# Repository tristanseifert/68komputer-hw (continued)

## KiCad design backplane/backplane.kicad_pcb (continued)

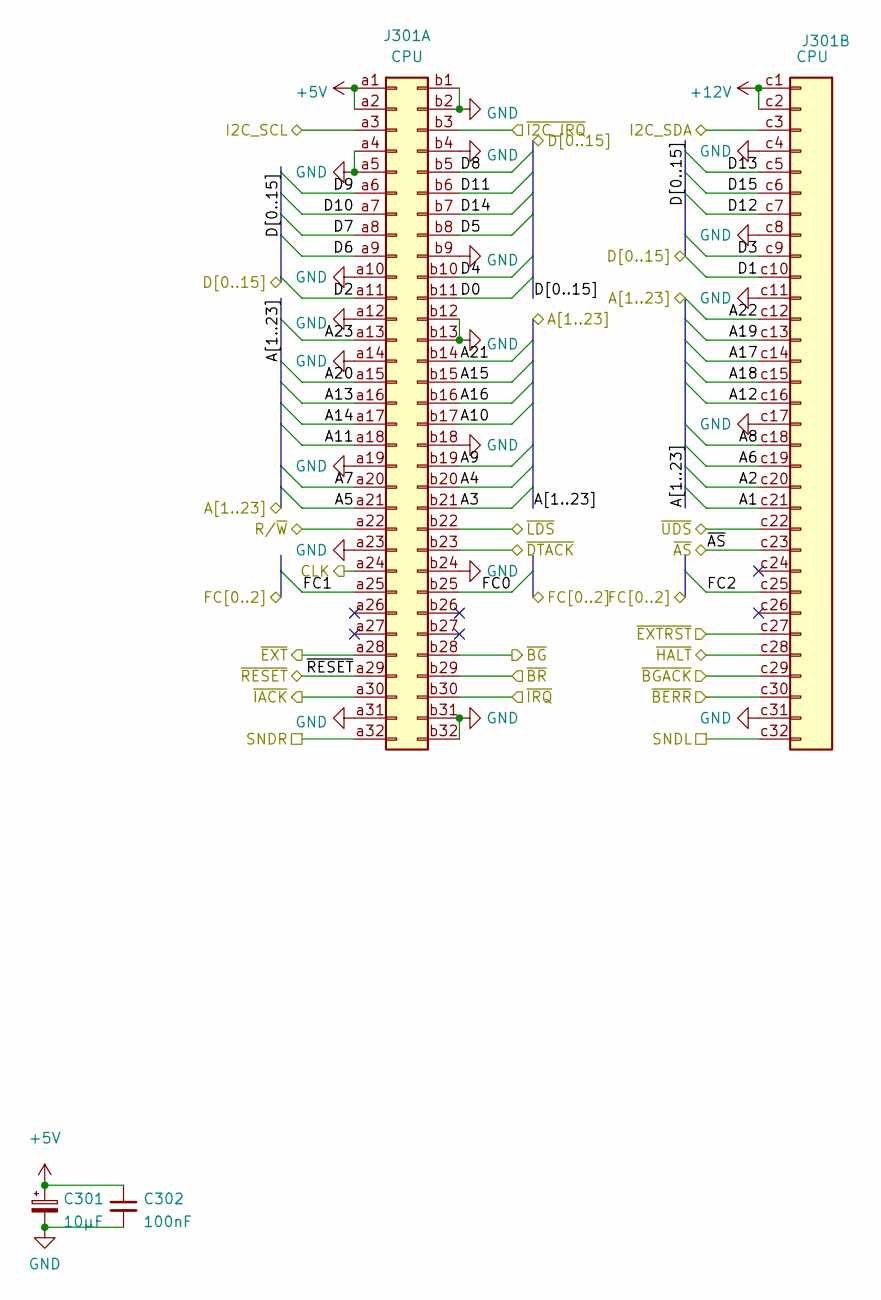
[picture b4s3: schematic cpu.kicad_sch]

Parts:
C301: 10µF; CP_EIA-3216-18_Kemet-A
C302: 100nF; C_0805_2012Metric
J301: CPU; DIN41612_C_3x32_Female_Vertical_THT

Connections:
+5V: C301.1, C302.1, J301.a1, J301.a2; also elsewhere on the board
+12V: J301.c1, J301.c2; also elsewhere on the board
/A1: J301.c21; also elsewhere on the board
/A2: J301.c20; also elsewhere on the board
/A3: J301.b21; also elsewhere on the board
/A4: J301.b20; also elsewhere on the board
/A5: J301.a21; also elsewhere on the board
/A6: J301.c19; also elsewhere on the board
/A7: J301.a20; also elsewhere on the board
/A8: J301.c18; also elsewhere on the board
/A9: J301.b19; also elsewhere on the board
/A10: J301.b17; also elsewhere on the board
/A11: J301.a18; also elsewhere on the board
/A12: J301.c16; also elsewhere on the board
/A13: J301.a16; also elsewhere on the board
/A14: J301.a17; also elsewhere on the board
/A15: J301.b15; also elsewhere on the board
/A16: J301.b16; also elsewhere on the board
/A17: J301.c14; also elsewhere on the board
/A18: J301.c15; also elsewhere on the board
/A19: J301.c13; also elsewhere on the board
/A20: J301.a15; also elsewhere on the board
/A21: J301.b14; also elsewhere on the board
/A22: J301.c12; also elsewhere on the board
/A23: J301.a13; also elsewhere on the board
/CPU Board/CLK: J301.a24
/CPU Board/SNDL: J301.c32
/CPU Board/SNDR: J301.a32
/D0: J301.b11; also elsewhere on the board
/D1: J301.c10; also elsewhere on the board
/D2: J301.a11; also elsewhere on the board
/D3: J301.c9; also elsewhere on the board
/D4: J301.b10; also elsewhere on the board
/D5: J301.b8; also elsewhere on the board
/D6: J301.a9; also elsewhere on the board
/D7: J301.a8; also elsewhere on the board
/D8: J301.b5; also elsewhere on the board
/D9: J301.a6; also elsewhere on the board
/D10: J301.a7; also elsewhere on the board
/D11: J301.b6; also elsewhere on the board
/D12: J301.c7; also elsewhere on the board
/D13: J301.c5; also elsewhere on the board
/D14: J301.b7; also elsewhere on the board
/D15: J301.c6; also elsewhere on the board
/FC0: J301.b25; also elsewhere on the board
/FC1: J301.a25; also elsewhere on the board
/FC2: J301.c25; also elsewhere on the board
/I2C_SCL: J301.a3; also elsewhere on the board
/I2C_SDA: J301.c3; also elsewhere on the board
/R/~W: J301.a22; also elsewhere on the board
/~AS: J301.c23; also elsewhere on the board
/~BERR: J301.c30; also elsewhere on the board
/~BGACK: J301.c29; also elsewhere on the board
/~BG: J301.b28; also elsewhere on the board
/~BR: J301.b29; also elsewhere on the board
/~DTACK: J301.b23; also elsewhere on the board
/~EXTRST: J301.c27; also elsewhere on the board
/~EXT: J301.a28; also elsewhere on the board
/~HALT: J301.c28; also elsewhere on the board
/~I2C_IRQ: J301.b3
/~IACK: J301.a30; also elsewhere on the board
/~IRQ: J301.b30; also elsewhere on the board
/~LDS: J301.b22; also elsewhere on the board
/~RESET: J301.a29; also elsewhere on the board
/~UDS: J301.c22; also elsewhere on the board
GND: C301.2, C302.2, J301.a4, J301.a5, J301.a10, J301.a12, J301.a14, J301.a19, J301.a23, J301.a31, J301.b1, J301.b2, J301.b4, J301.b9, J301.b12, J301.b13, J301.b18, J301.b24, J301.b31, J301.b32, J301.c4, J301.c8, J301.c11, J301.c17, J301.c31; also elsewhere on the board

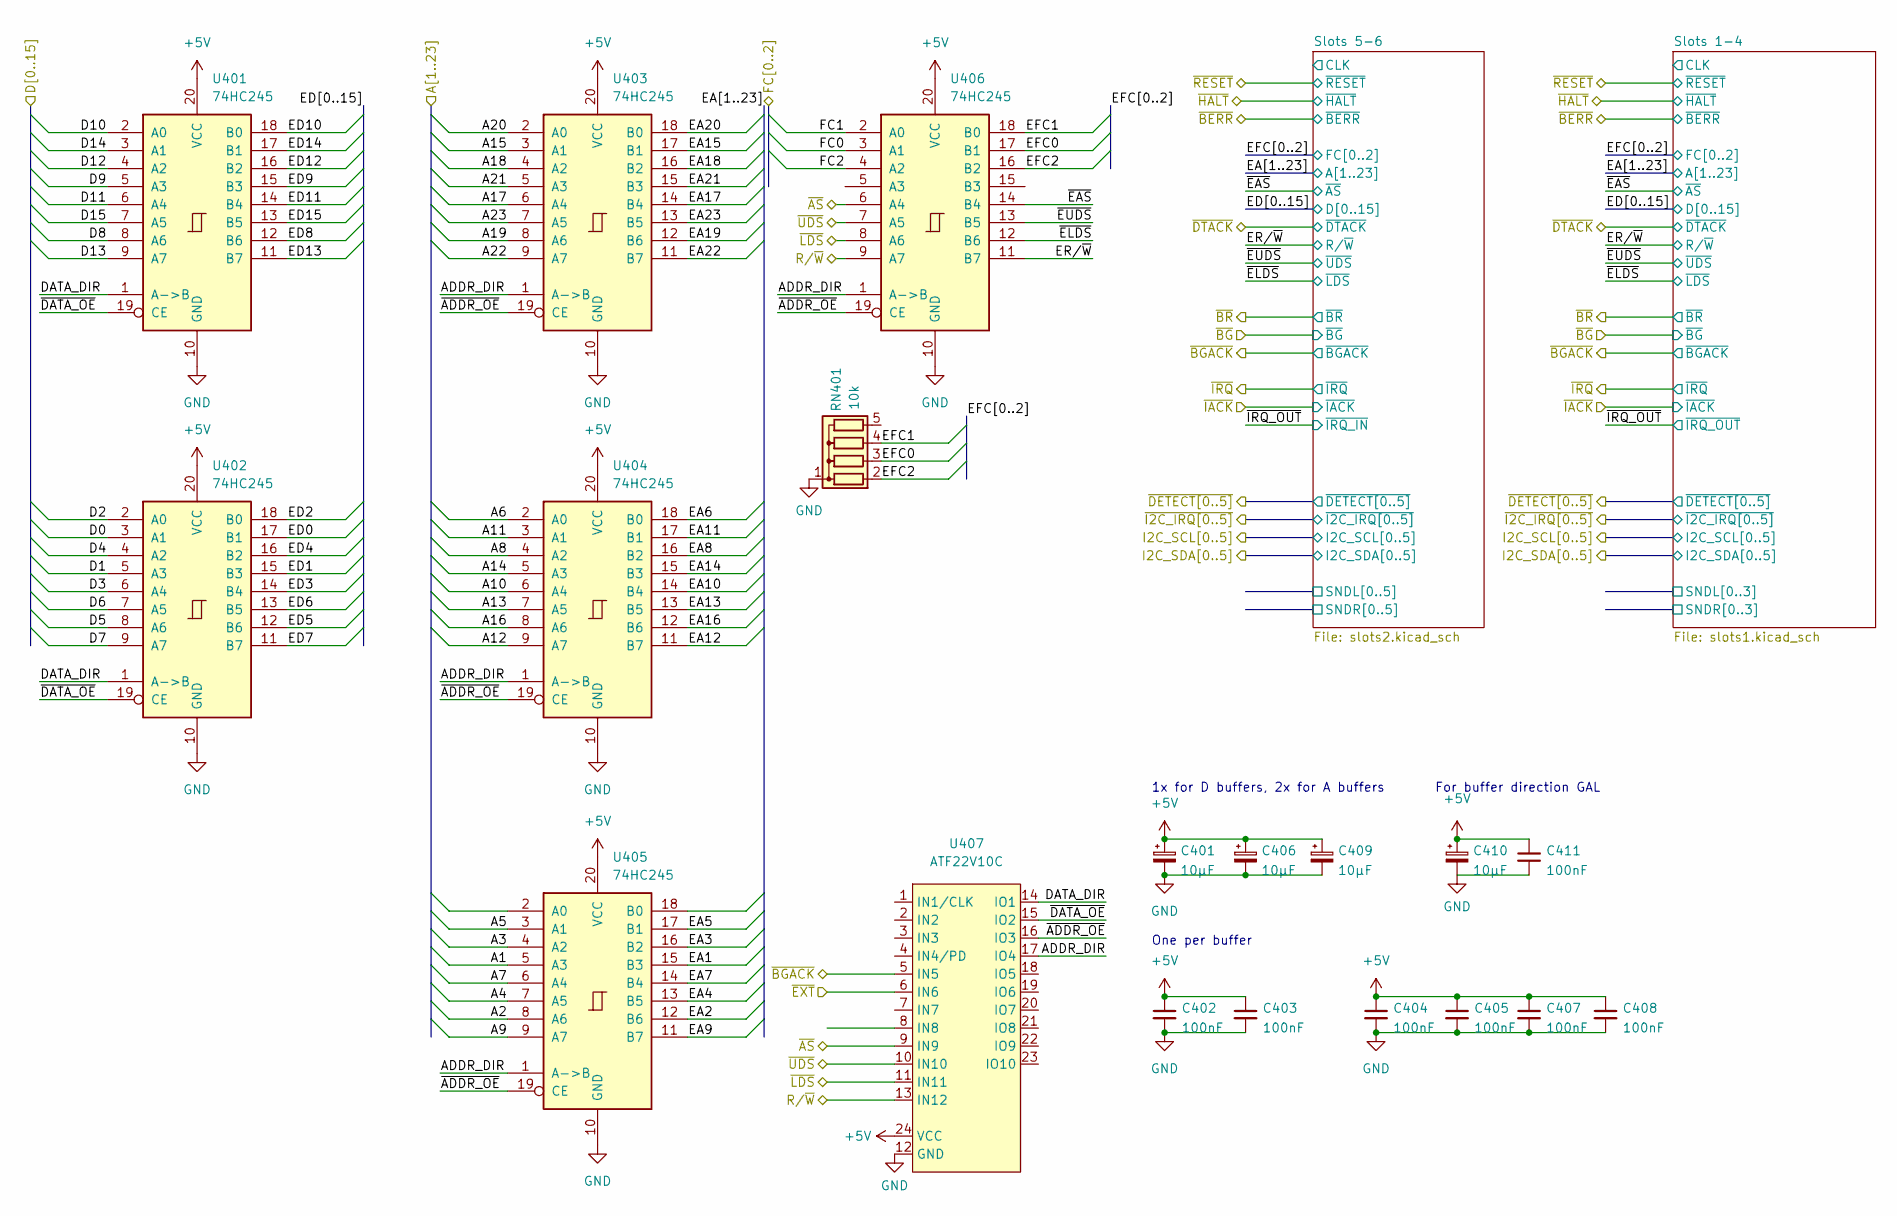
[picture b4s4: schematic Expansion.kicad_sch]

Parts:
C401, C406, C409, C410: 10µF; CP_EIA-3216-18_Kemet-A; MPN TAJA106K016RNJV
C402, C403, C404, C405, C407, C408, C411: 100nF; C_0805_2012Metric
RN401: 10k; R_Array_SIP5; MPN 4605X-101-103LF
U401, U402, U403, U404, U405, U406: 74HC245; TSSOP-20_4.4x6.5mm_P0.65mm; MPN 74HC245PW,118
U407: ATF22V10C; DIP-24_W7.62mm_Socket

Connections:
+5V: C401.1, C402.1, C403.1, C404.1, C405.1, C406.1, C407.1, C408.1, C409.1, C410.1, C411.1, U401.20 (VCC), U402.20 (VCC), U403.20 (VCC), U404.20 (VCC), U405.20 (VCC), U406.20 (VCC), U407.24 (VCC); also elsewhere on the board
/A1: U405.5 (A3); also elsewhere on the board
/A2: U405.8 (A6); also elsewhere on the board
/A3: U405.4 (A2); also elsewhere on the board
/A4: U405.7 (A5); also elsewhere on the board
/A5: U405.3 (A1); also elsewhere on the board
/A6: U404.2 (A0); also elsewhere on the board
/A7: U405.6 (A4); also elsewhere on the board
/A8: U404.4 (A2); also elsewhere on the board
/A9: U405.9 (A7); also elsewhere on the board
/A10: U404.6 (A4); also elsewhere on the board
/A11: U404.3 (A1); also elsewhere on the board
/A12: U404.9 (A7); also elsewhere on the board
/A13: U404.7 (A5); also elsewhere on the board
/A14: U404.5 (A3); also elsewhere on the board
/A15: U403.3 (A1); also elsewhere on the board
/A16: U404.8 (A6); also elsewhere on the board
/A17: U403.6 (A4); also elsewhere on the board
/A18: U403.4 (A2); also elsewhere on the board
/A19: U403.8 (A6); also elsewhere on the board
/A20: U403.2 (A0); also elsewhere on the board
/A21: U403.5 (A3); also elsewhere on the board
/A22: U403.9 (A7); also elsewhere on the board
/A23: U403.7 (A5); also elsewhere on the board
/D0: U402.3 (A1); also elsewhere on the board
/D1: U402.5 (A3); also elsewhere on the board
/D2: U402.2 (A0); also elsewhere on the board
/D3: U402.6 (A4); also elsewhere on the board
/D4: U402.4 (A2); also elsewhere on the board
/D5: U402.8 (A6); also elsewhere on the board
/D6: U402.7 (A5); also elsewhere on the board
/D7: U402.9 (A7); also elsewhere on the board
/D8: U401.8 (A6); also elsewhere on the board
/D9: U401.5 (A3); also elsewhere on the board
/D10: U401.2 (A0); also elsewhere on the board
/D11: U401.6 (A4); also elsewhere on the board
/D12: U401.4 (A2); also elsewhere on the board
/D13: U401.9 (A7); also elsewhere on the board
/D14: U401.3 (A1); also elsewhere on the board
/D15: U401.7 (A5); also elsewhere on the board
/Expansion Slots/ADDR_DIR: U403.1 (A->B), U404.1 (A->B), U405.1 (A->B), U406.1 (A->B), U407.17 (IO4)
/Expansion Slots/DATA_DIR: U401.1 (A->B), U402.1 (A->B), U407.14 (IO1)
/Expansion Slots/EA1: U405.15 (B3); also elsewhere on the board
/Expansion Slots/EA2: U405.12 (B6); also elsewhere on the board
/Expansion Slots/EA3: U405.16 (B2); also elsewhere on the board
/Expansion Slots/EA4: U405.13 (B5); also elsewhere on the board
/Expansion Slots/EA5: U405.17 (B1); also elsewhere on the board
/Expansion Slots/EA6: U404.18 (B0); also elsewhere on the board
/Expansion Slots/EA7: U405.14 (B4); also elsewhere on the board
/Expansion Slots/EA8: U404.16 (B2); also elsewhere on the board
/Expansion Slots/EA9: U405.11 (B7); also elsewhere on the board
/Expansion Slots/EA10: U404.14 (B4); also elsewhere on the board
/Expansion Slots/EA11: U404.17 (B1); also elsewhere on the board
/Expansion Slots/EA12: U404.11 (B7); also elsewhere on the board
/Expansion Slots/EA13: U404.13 (B5); also elsewhere on the board
/Expansion Slots/EA14: U404.15 (B3); also elsewhere on the board
/Expansion Slots/EA15: U403.17 (B1); also elsewhere on the board
/Expansion Slots/EA16: U404.12 (B6); also elsewhere on the board
/Expansion Slots/EA17: U403.14 (B4); also elsewhere on the board
/Expansion Slots/EA18: U403.16 (B2); also elsewhere on the board
/Expansion Slots/EA19: U403.12 (B6); also elsewhere on the board
/Expansion Slots/EA20: U403.18 (B0); also elsewhere on the board
/Expansion Slots/EA21: U403.15 (B3); also elsewhere on the board
/Expansion Slots/EA22: U403.11 (B7); also elsewhere on the board
/Expansion Slots/EA23: U403.13 (B5); also elsewhere on the board
/Expansion Slots/ED0: U402.17 (B1); also elsewhere on the board
/Expansion Slots/ED1: U402.15 (B3); also elsewhere on the board
/Expansion Slots/ED2: U402.18 (B0); also elsewhere on the board
/Expansion Slots/ED3: U402.14 (B4); also elsewhere on the board
/Expansion Slots/ED4: U402.16 (B2); also elsewhere on the board
/Expansion Slots/ED5: U402.12 (B6); also elsewhere on the board
/Expansion Slots/ED6: U402.13 (B5); also elsewhere on the board
/Expansion Slots/ED7: U402.11 (B7); also elsewhere on the board
/Expansion Slots/ED8: U401.12 (B6); also elsewhere on the board
/Expansion Slots/ED9: U401.15 (B3); also elsewhere on the board
/Expansion Slots/ED10: U401.18 (B0); also elsewhere on the board
/Expansion Slots/ED11: U401.14 (B4); also elsewhere on the board
/Expansion Slots/ED12: U401.16 (B2); also elsewhere on the board
/Expansion Slots/ED13: U401.11 (B7); also elsewhere on the board
/Expansion Slots/ED14: U401.17 (B1); also elsewhere on the board
/Expansion Slots/ED15: U401.13 (B5); also elsewhere on the board
/Expansion Slots/EFC0: RN401.3 (R2), U406.17 (B1); also elsewhere on the board
/Expansion Slots/EFC1: RN401.4 (R3), U406.18 (B0); also elsewhere on the board
/Expansion Slots/EFC2: RN401.2 (R1), U406.16 (B2); also elsewhere on the board
/Expansion Slots/ER/~W: U406.11 (B7); also elsewhere on the board
/Expansion Slots/~ADDR_OE: U403.19 (CE), U404.19 (CE), U405.19 (CE), U406.19 (CE), U407.16 (IO3)
/Expansion Slots/~DATA_OE: U401.19 (CE), U402.19 (CE), U407.15 (IO2)
/Expansion Slots/~EAS: U406.14 (B4); also elsewhere on the board
/Expansion Slots/~ELDS: U406.12 (B6); also elsewhere on the board
/Expansion Slots/~EUDS: U406.13 (B5); also elsewhere on the board
/FC0: U406.3 (A1); also elsewhere on the board
/FC1: U406.2 (A0); also elsewhere on the board
/FC2: U406.4 (A2); also elsewhere on the board
/R/~W: U406.9 (A7), U407.13 (IN12); also elsewhere on the board
/~AS: U406.6 (A4), U407.9 (IN9); also elsewhere on the board
/~BGACK: U407.5 (IN5); also elsewhere on the board
/~EXT: U407.6 (IN6); also elsewhere on the board
/~LDS: U406.8 (A6), U407.11 (IN11); also elsewhere on the board
/~UDS: U406.7 (A5), U407.10 (IN10); also elsewhere on the board
GND: C401.2, C402.2, C403.2, C404.2, C405.2, C406.2, C407.2, C408.2, C409.2, C410.2, C411.2, RN401.1 (common), U401.10 (GND), U402.10 (GND), U403.10 (GND), U404.10 (GND), U405.10 (GND), U406.10 (GND), U407.12 (GND); also elsewhere on the board

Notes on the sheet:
One per buffer
1x for D buffers, 2x for A buffers
For buffer direction GAL

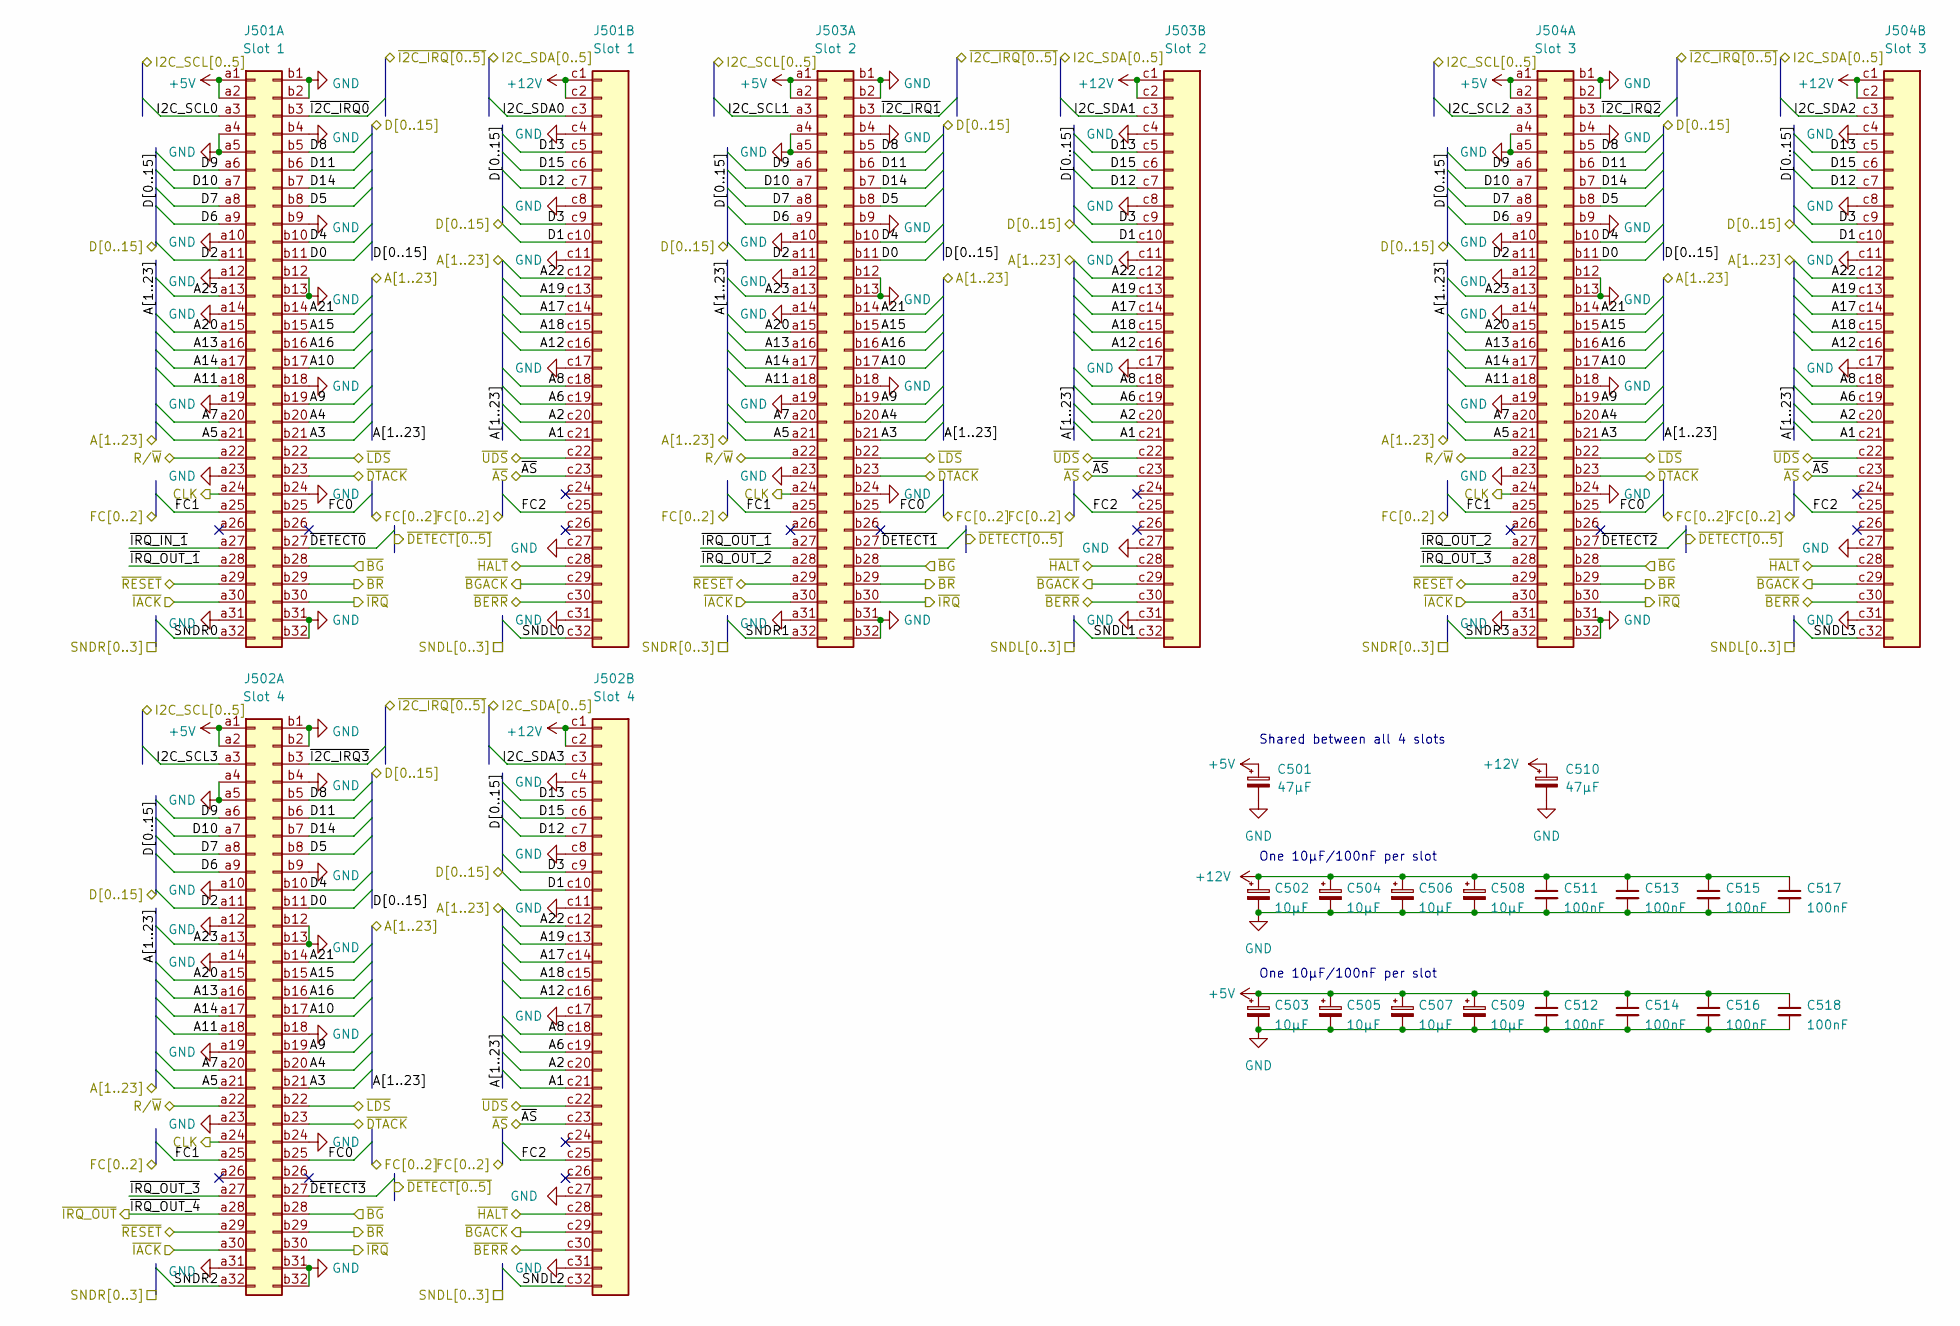
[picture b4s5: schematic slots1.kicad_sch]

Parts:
C501, C510: 47µF; CP_Elec_6.3x5.7; MPN A768EB476M1ELAS042
C502, C504, C506, C508: 10µF; CP_Radial_D4.0mm_P1.50mm; MPN ESY106M035AB2AA
C503, C505, C507, C509: 10µF; CP_EIA-3216-18_Kemet-A; MPN TAJA106K016RNJV
C511, C512, C513, C514, C515, C516, C517, C518: 100nF; C_0805_2012Metric
J501: Slot 1; DIN41612_C_3x32_Female_Vertical_THT
J502: Slot 4; DIN41612_C_3x32_Female_Vertical_THT
J503: Slot 2; DIN41612_C_3x32_Female_Vertical_THT
J504: Slot 3; DIN41612_C_3x32_Female_Vertical_THT; MPN 86093968124H55V1LF

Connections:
+5V: C501.1, C503.1, C505.1, C507.1, C509.1, C512.1, C514.1, C516.1, C518.1, J501.a1, J501.a2, J502.a1, J502.a2, J503.a1, J503.a2, J504.a1, J504.a2; also elsewhere on the board
+12V: C502.1, C504.1, C506.1, C508.1, C510.1, C511.1, C513.1, C515.1, C517.1, J501.c1, J501.c2, J502.c1, J502.c2, J503.c1, J503.c2, J504.c1, J504.c2; also elsewhere on the board
/Expansion Slots/EA1: J501.c21, J502.c21, J503.c21, J504.c21; also elsewhere on the board
/Expansion Slots/EA2: J501.c20, J502.c20, J503.c20, J504.c20; also elsewhere on the board
/Expansion Slots/EA3: J501.b21, J502.b21, J503.b21, J504.b21; also elsewhere on the board
/Expansion Slots/EA4: J501.b20, J502.b20, J503.b20, J504.b20; also elsewhere on the board
/Expansion Slots/EA5: J501.a21, J502.a21, J503.a21, J504.a21; also elsewhere on the board
/Expansion Slots/EA6: J501.c19, J502.c19, J503.c19, J504.c19; also elsewhere on the board
/Expansion Slots/EA7: J501.a20, J502.a20, J503.a20, J504.a20; also elsewhere on the board
/Expansion Slots/EA8: J501.c18, J502.c18, J503.c18, J504.c18; also elsewhere on the board
/Expansion Slots/EA9: J501.b19, J502.b19, J503.b19, J504.b19; also elsewhere on the board
/Expansion Slots/EA10: J501.b17, J502.b17, J503.b17, J504.b17; also elsewhere on the board
/Expansion Slots/EA11: J501.a18, J502.a18, J503.a18, J504.a18; also elsewhere on the board
/Expansion Slots/EA12: J501.c16, J502.c16, J503.c16, J504.c16; also elsewhere on the board
/Expansion Slots/EA13: J501.a16, J502.a16, J503.a16, J504.a16; also elsewhere on the board
/Expansion Slots/EA14: J501.a17, J502.a17, J503.a17, J504.a17; also elsewhere on the board
/Expansion Slots/EA15: J501.b15, J502.b15, J503.b15, J504.b15; also elsewhere on the board
/Expansion Slots/EA16: J501.b16, J502.b16, J503.b16, J504.b16; also elsewhere on the board
/Expansion Slots/EA17: J501.c14, J502.c14, J503.c14, J504.c14; also elsewhere on the board
/Expansion Slots/EA18: J501.c15, J502.c15, J503.c15, J504.c15; also elsewhere on the board
/Expansion Slots/EA19: J501.c13, J502.c13, J503.c13, J504.c13; also elsewhere on the board
/Expansion Slots/EA20: J501.a15, J502.a15, J503.a15, J504.a15; also elsewhere on the board
/Expansion Slots/EA21: J501.b14, J502.b14, J503.b14, J504.b14; also elsewhere on the board
/Expansion Slots/EA22: J501.c12, J502.c12, J503.c12, J504.c12; also elsewhere on the board
/Expansion Slots/EA23: J501.a13, J502.a13, J503.a13, J504.a13; also elsewhere on the board
/Expansion Slots/ED0: J501.b11, J502.b11, J503.b11, J504.b11; also elsewhere on the board
/Expansion Slots/ED1: J501.c10, J502.c10, J503.c10, J504.c10; also elsewhere on the board
/Expansion Slots/ED2: J501.a11, J502.a11, J503.a11, J504.a11; also elsewhere on the board
/Expansion Slots/ED3: J501.c9, J502.c9, J503.c9, J504.c9; also elsewhere on the board
/Expansion Slots/ED4: J501.b10, J502.b10, J503.b10, J504.b10; also elsewhere on the board
/Expansion Slots/ED5: J501.b8, J502.b8, J503.b8, J504.b8; also elsewhere on the board
/Expansion Slots/ED6: J501.a9, J502.a9, J503.a9, J504.a9; also elsewhere on the board
/Expansion Slots/ED7: J501.a8, J502.a8, J503.a8, J504.a8; also elsewhere on the board
/Expansion Slots/ED8: J501.b5, J502.b5, J503.b5, J504.b5; also elsewhere on the board
/Expansion Slots/ED9: J501.a6, J502.a6, J503.a6, J504.a6; also elsewhere on the board
/Expansion Slots/ED10: J501.a7, J502.a7, J503.a7, J504.a7; also elsewhere on the board
/Expansion Slots/ED11: J501.b6, J502.b6, J503.b6, J504.b6; also elsewhere on the board
/Expansion Slots/ED12: J501.c7, J502.c7, J503.c7, J504.c7; also elsewhere on the board
/Expansion Slots/ED13: J501.c5, J502.c5, J503.c5, J504.c5; also elsewhere on the board
/Expansion Slots/ED14: J501.b7, J502.b7, J503.b7, J504.b7; also elsewhere on the board
/Expansion Slots/ED15: J501.c6, J502.c6, J503.c6, J504.c6; also elsewhere on the board
/Expansion Slots/EFC0: J501.b25, J502.b25, J503.b25, J504.b25; also elsewhere on the board
/Expansion Slots/EFC1: J501.a25, J502.a25, J503.a25, J504.a25; also elsewhere on the board
/Expansion Slots/EFC2: J501.c25, J502.c25, J503.c25, J504.c25; also elsewhere on the board
/Expansion Slots/ER/~W: J501.a22, J502.a22, J503.a22, J504.a22; also elsewhere on the board
/Expansion Slots/I2C_SCL0: J501.a3
/Expansion Slots/I2C_SCL1: J503.a3
/Expansion Slots/I2C_SCL2: J504.a3
/Expansion Slots/I2C_SCL3: J502.a3
/Expansion Slots/I2C_SDA0: J501.c3
/Expansion Slots/I2C_SDA1: J503.c3
/Expansion Slots/I2C_SDA2: J504.c3
/Expansion Slots/I2C_SDA3: J502.c3
/Expansion Slots/Slots 1-4/CLK: J501.a24, J502.a24, J503.a24, J504.a24
/Expansion Slots/Slots 1-4/SNDL0: J501.c32
/Expansion Slots/Slots 1-4/SNDL1: J503.c32
/Expansion Slots/Slots 1-4/SNDL2: J502.c32
/Expansion Slots/Slots 1-4/SNDL3: J504.c32
/Expansion Slots/Slots 1-4/SNDR0: J501.a32
/Expansion Slots/Slots 1-4/SNDR1: J503.a32
/Expansion Slots/Slots 1-4/SNDR2: J502.a32
/Expansion Slots/Slots 1-4/SNDR3: J504.a32
/Expansion Slots/Slots 1-4/~IRQ_IN_1: J501.a27
/Expansion Slots/Slots 1-4/~IRQ_OUT_1: J501.a28, J503.a27
/Expansion Slots/Slots 1-4/~IRQ_OUT_2: J503.a28, J504.a27
/Expansion Slots/Slots 1-4/~IRQ_OUT_3: J502.a27, J504.a28
/Expansion Slots/~EAS: J501.c23, J502.c23, J503.c23, J504.c23; also elsewhere on the board
/Expansion Slots/~ELDS: J501.b22, J502.b22, J503.b22, J504.b22; also elsewhere on the board
/Expansion Slots/~EUDS: J501.c22, J502.c22, J503.c22, J504.c22; also elsewhere on the board
/Expansion Slots/~I2C_IRQ0: J501.b3
/Expansion Slots/~I2C_IRQ1: J503.b3
/Expansion Slots/~I2C_IRQ2: J504.b3
/Expansion Slots/~I2C_IRQ3: J502.b3
/Expansion Slots/~IRQ_OUT: J502.a28; also elsewhere on the board
/~BERR: J501.c30, J502.c30, J503.c30, J504.c30; also elsewhere on the board
/~BGACK: J501.c29, J502.c29, J503.c29, J504.c29; also elsewhere on the board
/~BG: J501.b28, J502.b28, J503.b28, J504.b28; also elsewhere on the board
/~BR: J501.b29, J502.b29, J503.b29, J504.b29; also elsewhere on the board
/~DETECT0: J501.b27; also elsewhere on the board
/~DETECT1: J503.b27; also elsewhere on the board
/~DETECT2: J504.b27; also elsewhere on the board
/~DETECT3: J502.b27; also elsewhere on the board
/~DTACK: J501.b23, J502.b23, J503.b23, J504.b23; also elsewhere on the board
/~HALT: J501.c28, J502.c28, J503.c28, J504.c28; also elsewhere on the board
/~IACK: J501.a30, J502.a30, J503.a30, J504.a30; also elsewhere on the board
/~IRQ: J501.b30, J502.b30, J503.b30, J504.b30; also elsewhere on the board
/~RESET: J501.a29, J502.a29, J503.a29, J504.a29; also elsewhere on the board
GND: C501.2, C502.2, C503.2, C504.2, C505.2, C506.2, C507.2, C508.2, C509.2, C510.2, C511.2, C512.2, C513.2, C514.2, C515.2, C516.2, C517.2, C518.2, J501.a4, J501.a5, J501.a10, J501.a12, J501.a14, J501.a19, J501.a23, J501.a31, J501.b1, J501.b2, J501.b4, J501.b9, J501.b12, J501.b13, J501.b18, J501.b24, J501.b31, J501.b32, J501.c4, J501.c8, J501.c11, J501.c17, J501.c27, J501.c31, J502.a4, J502.a5, J502.a10, J502.a12, J502.a14, J502.a19, J502.a23, J502.a31, J502.b1, J502.b2, J502.b4, J502.b9, J502.b12, J502.b13, J502.b18, J502.b24, J502.b31, J502.b32, J502.c4, J502.c8, J502.c11, J502.c17, J502.c27, J502.c31, J503.a4, J503.a5, J503.a10, J503.a12, J503.a14, J503.a19, J503.a23, J503.a31, J503.b1, J503.b2, J503.b4, J503.b9, J503.b12, J503.b13, J503.b18, J503.b24, J503.b31, J503.b32, J503.c4, J503.c8, J503.c11, J503.c17, J503.c27, J503.c31, J504.a4, J504.a5, J504.a10, J504.a12, J504.a14, J504.a19, J504.a23, J504.a31, J504.b1, J504.b2, J504.b4, J504.b9, J504.b12, J504.b13, J504.b18, J504.b24, J504.b31, J504.b32, J504.c4, J504.c8, J504.c11, J504.c17, J504.c27, J504.c31; also elsewhere on the board

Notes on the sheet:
One 10µF/100nF per slot
Shared between all 4 slots

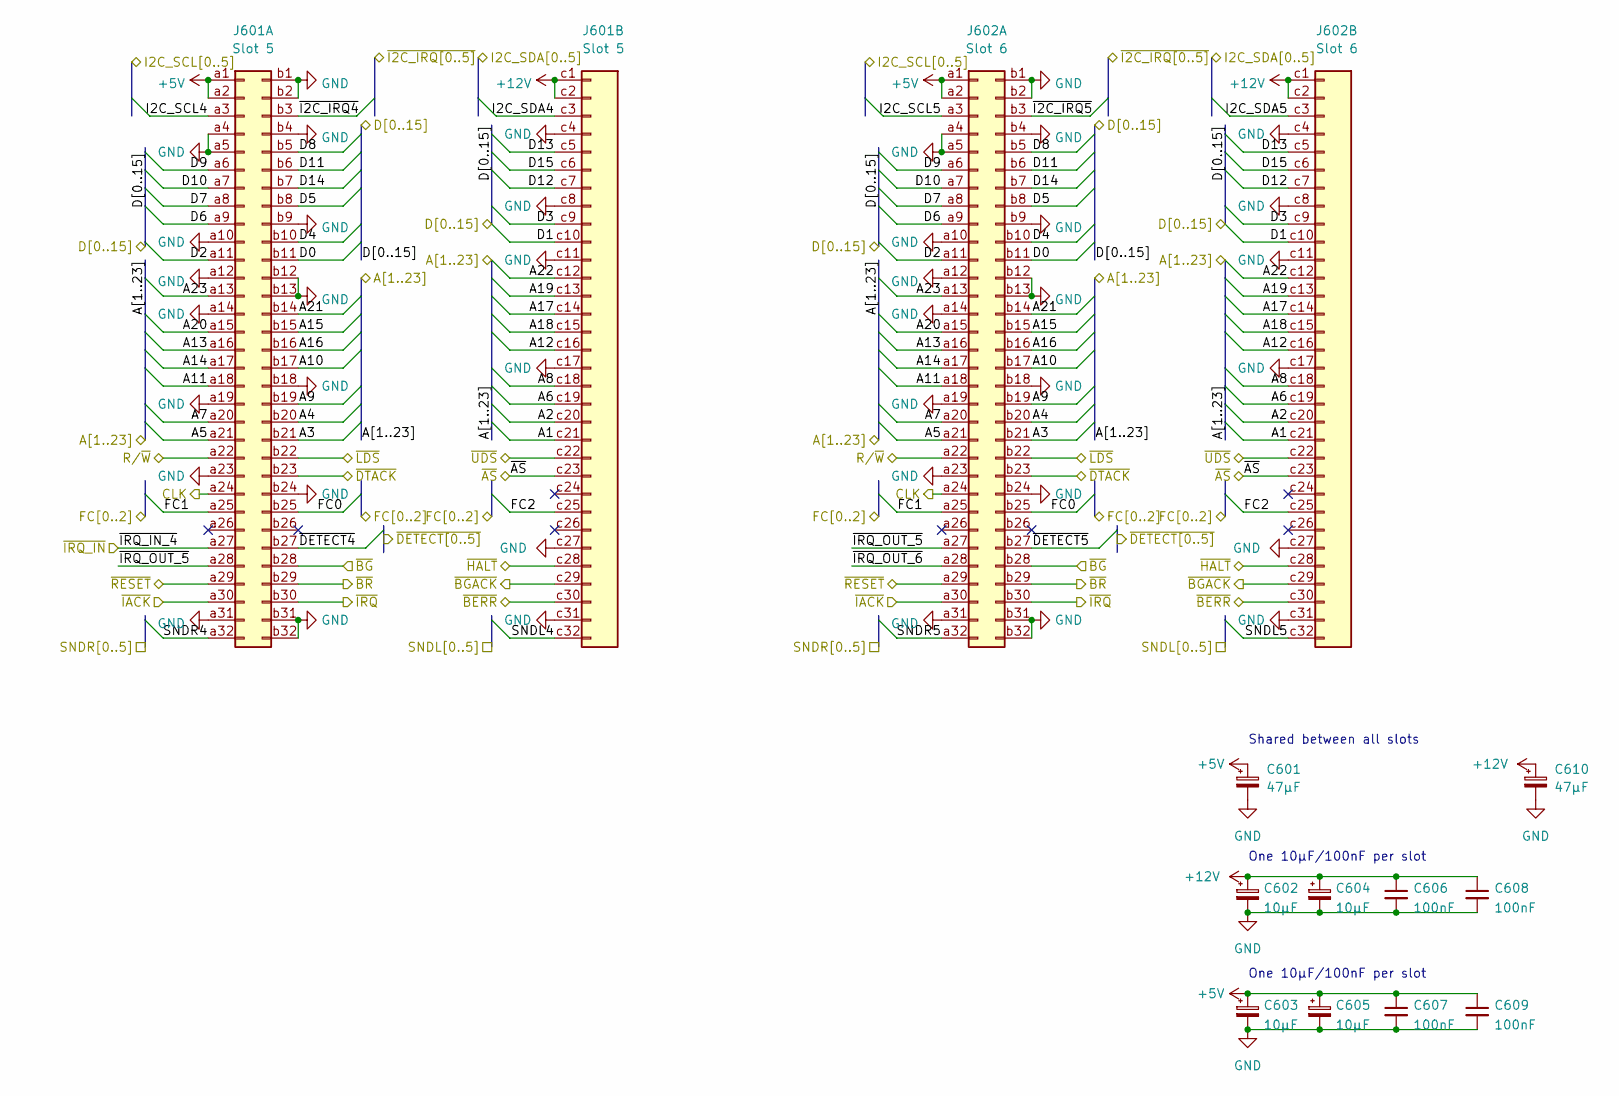
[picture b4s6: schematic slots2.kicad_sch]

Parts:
C601, C610: 47µF; CP_Elec_6.3x5.7; MPN A768EB476M1ELAS042
C602, C604: 10µF; CP_Radial_D4.0mm_P1.50mm; MPN ESY106M035AB2AA
C603, C605: 10µF; CP_EIA-3216-18_Kemet-A; MPN TAJA106K016RNJV
C606, C607, C608, C609: 100nF; C_0805_2012Metric
J601: Slot 5; DIN41612_C_3x32_Female_Vertical_THT; MPN 86093968124H55V1LF
J602: Slot 6; DIN41612_C_3x32_Female_Vertical_THT; MPN 86093968124H55V1LF

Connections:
+5V: C601.1, C603.1, C605.1, C607.1, C609.1, J601.a1, J601.a2, J602.a1, J602.a2; also elsewhere on the board
+12V: C602.1, C604.1, C606.1, C608.1, C610.1, J601.c1, J601.c2, J602.c1, J602.c2; also elsewhere on the board
/Expansion Slots/EA1: J601.c21, J602.c21; also elsewhere on the board
/Expansion Slots/EA2: J601.c20, J602.c20; also elsewhere on the board
/Expansion Slots/EA3: J601.b21, J602.b21; also elsewhere on the board
/Expansion Slots/EA4: J601.b20, J602.b20; also elsewhere on the board
/Expansion Slots/EA5: J601.a21, J602.a21; also elsewhere on the board
/Expansion Slots/EA6: J601.c19, J602.c19; also elsewhere on the board
/Expansion Slots/EA7: J601.a20, J602.a20; also elsewhere on the board
/Expansion Slots/EA8: J601.c18, J602.c18; also elsewhere on the board
/Expansion Slots/EA9: J601.b19, J602.b19; also elsewhere on the board
/Expansion Slots/EA10: J601.b17, J602.b17; also elsewhere on the board
/Expansion Slots/EA11: J601.a18, J602.a18; also elsewhere on the board
/Expansion Slots/EA12: J601.c16, J602.c16; also elsewhere on the board
/Expansion Slots/EA13: J601.a16, J602.a16; also elsewhere on the board
/Expansion Slots/EA14: J601.a17, J602.a17; also elsewhere on the board
/Expansion Slots/EA15: J601.b15, J602.b15; also elsewhere on the board
/Expansion Slots/EA16: J601.b16, J602.b16; also elsewhere on the board
/Expansion Slots/EA17: J601.c14, J602.c14; also elsewhere on the board
/Expansion Slots/EA18: J601.c15, J602.c15; also elsewhere on the board
/Expansion Slots/EA19: J601.c13, J602.c13; also elsewhere on the board
/Expansion Slots/EA20: J601.a15, J602.a15; also elsewhere on the board
/Expansion Slots/EA21: J601.b14, J602.b14; also elsewhere on the board
/Expansion Slots/EA22: J601.c12, J602.c12; also elsewhere on the board
/Expansion Slots/EA23: J601.a13, J602.a13; also elsewhere on the board
/Expansion Slots/ED0: J601.b11, J602.b11; also elsewhere on the board
/Expansion Slots/ED1: J601.c10, J602.c10; also elsewhere on the board
/Expansion Slots/ED2: J601.a11, J602.a11; also elsewhere on the board
/Expansion Slots/ED3: J601.c9, J602.c9; also elsewhere on the board
/Expansion Slots/ED4: J601.b10, J602.b10; also elsewhere on the board
/Expansion Slots/ED5: J601.b8, J602.b8; also elsewhere on the board
/Expansion Slots/ED6: J601.a9, J602.a9; also elsewhere on the board
/Expansion Slots/ED7: J601.a8, J602.a8; also elsewhere on the board
/Expansion Slots/ED8: J601.b5, J602.b5; also elsewhere on the board
/Expansion Slots/ED9: J601.a6, J602.a6; also elsewhere on the board
/Expansion Slots/ED10: J601.a7, J602.a7; also elsewhere on the board
/Expansion Slots/ED11: J601.b6, J602.b6; also elsewhere on the board
/Expansion Slots/ED12: J601.c7, J602.c7; also elsewhere on the board
/Expansion Slots/ED13: J601.c5, J602.c5; also elsewhere on the board
/Expansion Slots/ED14: J601.b7, J602.b7; also elsewhere on the board
/Expansion Slots/ED15: J601.c6, J602.c6; also elsewhere on the board
/Expansion Slots/EFC0: J601.b25, J602.b25; also elsewhere on the board
/Expansion Slots/EFC1: J601.a25, J602.a25; also elsewhere on the board
/Expansion Slots/EFC2: J601.c25, J602.c25; also elsewhere on the board
/Expansion Slots/ER/~W: J601.a22, J602.a22; also elsewhere on the board
/Expansion Slots/I2C_SCL4: J601.a3
/Expansion Slots/I2C_SCL5: J602.a3
/Expansion Slots/I2C_SDA4: J601.c3
/Expansion Slots/I2C_SDA5: J602.c3
/Expansion Slots/Slots 5-6/CLK: J601.a24, J602.a24
/Expansion Slots/Slots 5-6/SNDL4: J601.c32
/Expansion Slots/Slots 5-6/SNDL5: J602.c32
/Expansion Slots/Slots 5-6/SNDR4: J601.a32
/Expansion Slots/Slots 5-6/SNDR5: J602.a32
/Expansion Slots/Slots 5-6/~IRQ_OUT_5: J601.a28, J602.a27
/Expansion Slots/Slots 5-6/~IRQ_OUT_6: J602.a28
/Expansion Slots/~EAS: J601.c23, J602.c23; also elsewhere on the board
/Expansion Slots/~ELDS: J601.b22, J602.b22; also elsewhere on the board
/Expansion Slots/~EUDS: J601.c22, J602.c22; also elsewhere on the board
/Expansion Slots/~I2C_IRQ4: J601.b3
/Expansion Slots/~I2C_IRQ5: J602.b3
/Expansion Slots/~IRQ_OUT: J601.a27; also elsewhere on the board
/~BERR: J601.c30, J602.c30; also elsewhere on the board
/~BGACK: J601.c29, J602.c29; also elsewhere on the board
/~BG: J601.b28, J602.b28; also elsewhere on the board
/~BR: J601.b29, J602.b29; also elsewhere on the board
/~DETECT4: J601.b27; also elsewhere on the board
/~DETECT5: J602.b27; also elsewhere on the board
/~DTACK: J601.b23, J602.b23; also elsewhere on the board
/~HALT: J601.c28, J602.c28; also elsewhere on the board
/~IACK: J601.a30, J602.a30; also elsewhere on the board
/~IRQ: J601.b30, J602.b30; also elsewhere on the board
/~RESET: J601.a29, J602.a29; also elsewhere on the board
GND: C601.2, C602.2, C603.2, C604.2, C605.2, C606.2, C607.2, C608.2, C609.2, C610.2, J601.a4, J601.a5, J601.a10, J601.a12, J601.a14, J601.a19, J601.a23, J601.a31, J601.b1, J601.b2, J601.b4, J601.b9, J601.b12, J601.b13, J601.b18, J601.b24, J601.b31, J601.b32, J601.c4, J601.c8, J601.c11, J601.c17, J601.c27, J601.c31, J602.a4, J602.a5, J602.a10, J602.a12, J602.a14, J602.a19, J602.a23, J602.a31, J602.b1, J602.b2, J602.b4, J602.b9, J602.b12, J602.b13, J602.b18, J602.b24, J602.b31, J602.b32, J602.c4, J602.c8, J602.c11, J602.c17, J602.c27, J602.c31; also elsewhere on the board

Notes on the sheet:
Shared between all slots
One 10µF/100nF per slot
